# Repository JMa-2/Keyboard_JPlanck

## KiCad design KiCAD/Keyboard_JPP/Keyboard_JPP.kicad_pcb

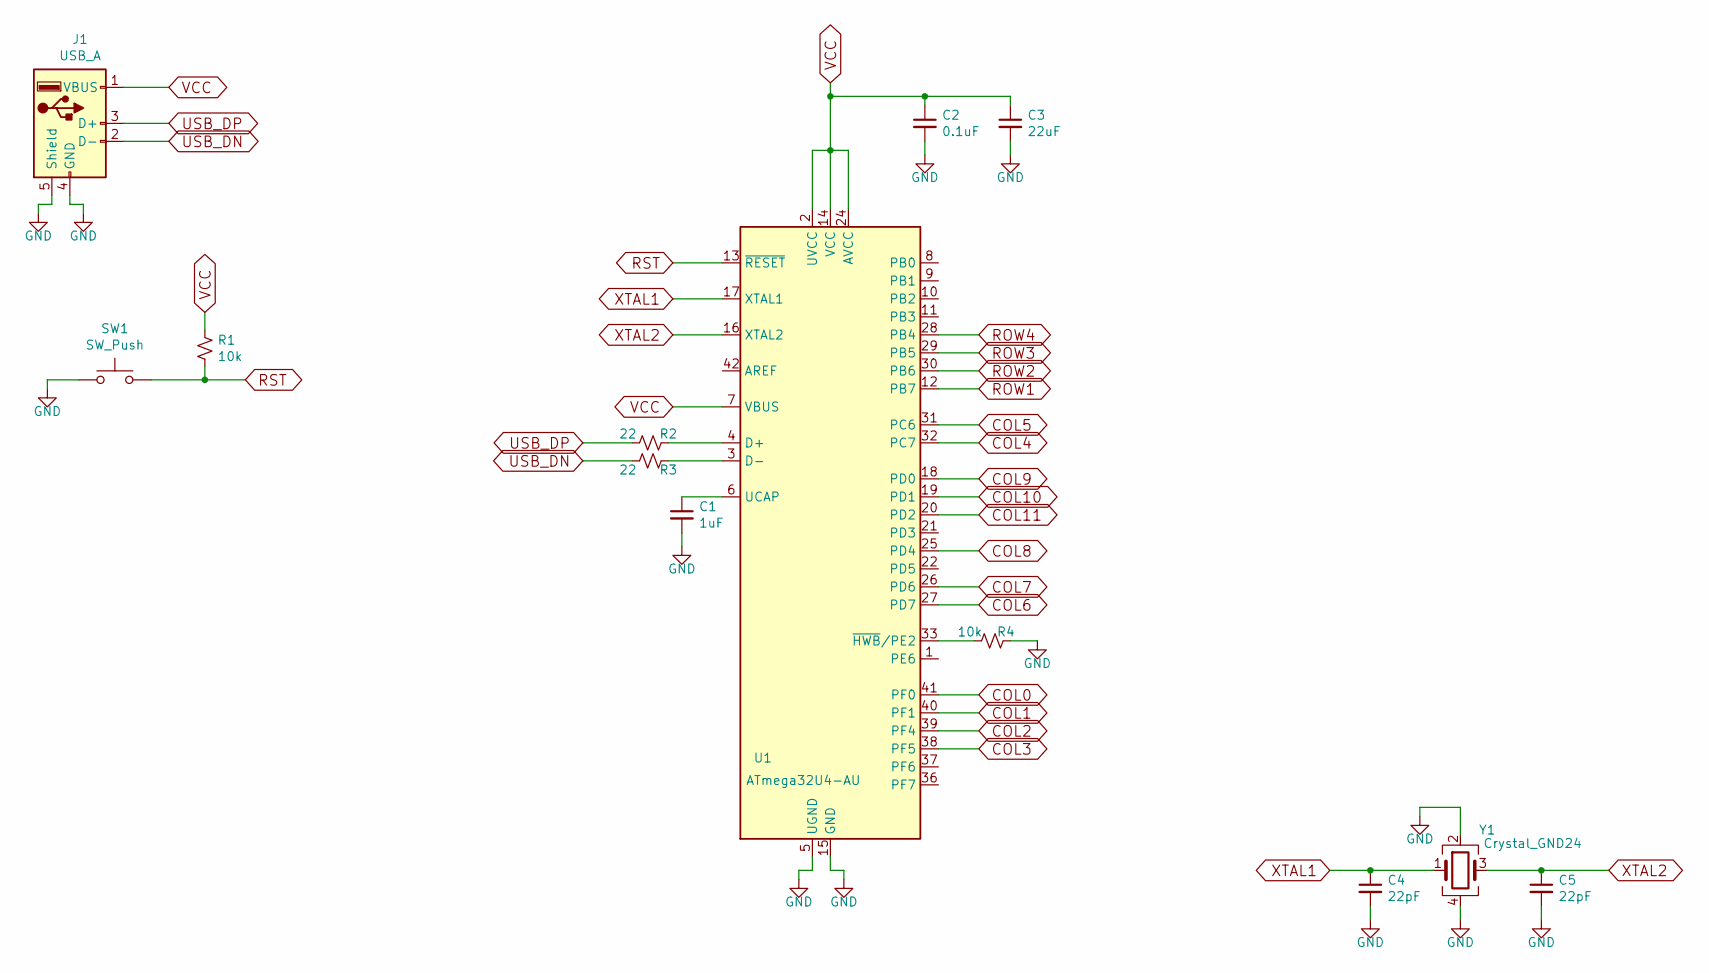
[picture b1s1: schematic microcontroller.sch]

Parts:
C1: 1uF; C_0603_1608Metric
C2: 0.1uF; C_0603_1608Metric
C3: 22uF; C_0603_1608Metric
C4, C5: 22pF; C_0603_1608Metric
J1: USB_A; USB_A_Molex_67643_Horizontal
R1, R4: 10k; R_0805_2012Metric
R2, R3: 22; R_0805_2012Metric
SW1: SW_Push; SW_Push_1P1T_NO_6x6mm_H9.5mm
U1: ATmega32U4-AU; TQFP-44_10x10mm_P0.8mm
Y1: Crystal_GND24; Crystal_SMD_3225-4Pin_3.2x2.5mm_HandSoldering

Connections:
COL0: U1.41 (PF0); also elsewhere on the board
COL1: U1.40 (PF1); also elsewhere on the board
COL2: U1.39 (PF4); also elsewhere on the board
COL3: U1.38 (PF5); also elsewhere on the board
COL4: U1.32 (PC7); also elsewhere on the board
COL5: U1.31 (PC6); also elsewhere on the board
COL6: U1.27 (PD7); also elsewhere on the board
COL7: U1.26 (PD6); also elsewhere on the board
COL8: U1.25 (PD4); also elsewhere on the board
COL9: U1.18 (PD0); also elsewhere on the board
COL10: U1.19 (PD1); also elsewhere on the board
COL11: U1.20 (PD2); also elsewhere on the board
GND: C1.2, C2.2, C3.2, C4.2, C5.2, J1.4 (GND), J1.5 (Shield), R4.1, SW1.1, U1.5 (UGND), U1.15 (GND), U1.23 (GND), U1.35 (GND), U1.43 (GND), Y1.2, Y1.4
unnamed: C1.1, U1.6 (UCAP)
unnamed: R2.1, U1.4 (D+)
unnamed: R3.1, U1.3 (D-)
unnamed: R4.2, U1.33 (~HWB~/PE2)
ROW1: U1.12 (PB7); also elsewhere on the board
ROW2: U1.30 (PB6); also elsewhere on the board
ROW3: U1.29 (PB5); also elsewhere on the board
ROW4: U1.28 (PB4); also elsewhere on the board
RST: R1.2, SW1.2, U1.13 (~RESET)
USB_DN: J1.2 (D-), R3.2
USB_DP: J1.3 (D+), R2.2
VCC: C2.1, C3.1, J1.1 (VBUS), R1.1, U1.2 (UVCC), U1.7 (VBUS), U1.14 (VCC), U1.24 (AVCC), U1.34 (VCC), U1.44 (AVCC)
XTAL1: C4.1, U1.17 (XTAL1), Y1.1
XTAL2: C5.1, U1.16 (XTAL2), Y1.3

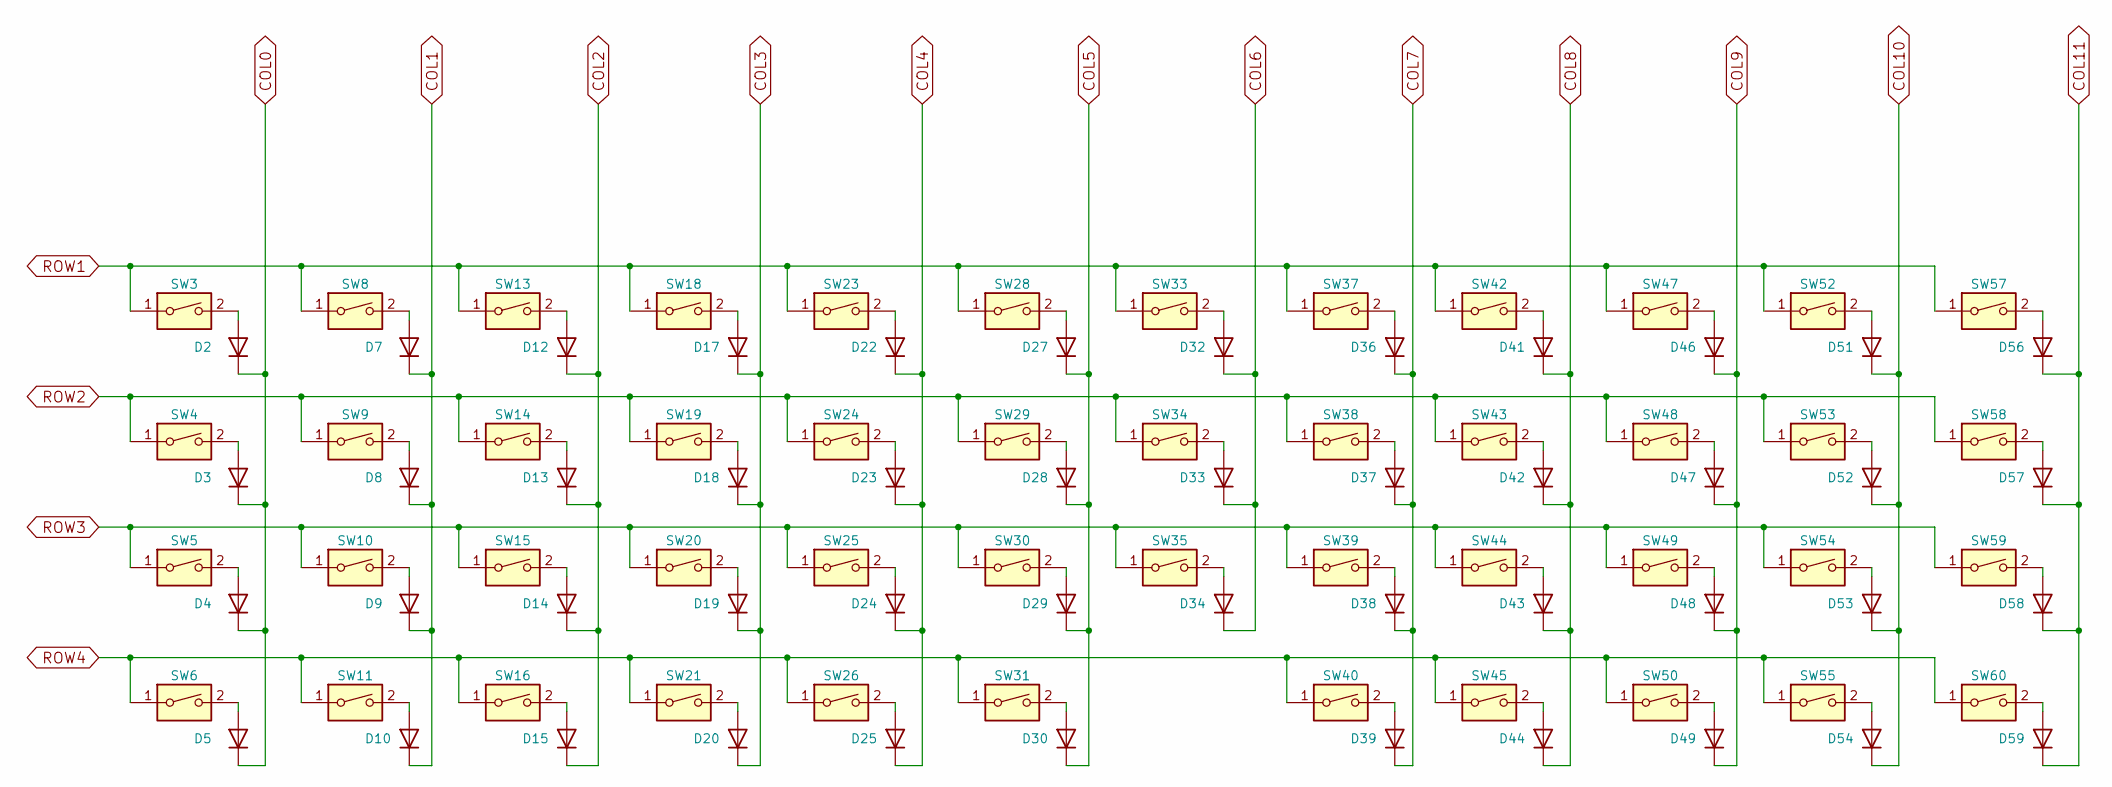
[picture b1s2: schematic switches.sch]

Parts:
D2, D3, D4, D5, D7, D8, D9, D10, D12, D13, D14, D15, D17, D18, D19, D20, D22, D23, D24, D25, D27, D28, D29, D30, D32, D33, D34, D36, D37, D38, D39, D41, D42, D43, D44, D46, D47, D48, D49, D51, D52, D53, D54, D56, D57, D58, D59: 1N4148; D_DO-35_SOD27_P7.62mm_Horizontal
SW3, SW4, SW5, SW6, SW8, SW9, SW10, SW11, SW13, SW14, SW15, SW16, SW18, SW19, SW20, SW21, SW23, SW24, SW25, SW26, SW28, SW29, SW30, SW31, SW33, SW34, SW35, SW37, SW38, SW39, SW40, SW42, SW43, SW44, SW45, SW47, SW48, SW49, SW50, SW52, SW53, SW54, SW55, SW57, SW58, SW59, SW60: SW_DIP_x01; Kailh_socket_MX

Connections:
COL0: D2.1 (K), D3.1 (K), D4.1 (K), D5.1 (K); also elsewhere on the board
COL1: D7.1 (K), D8.1 (K), D9.1 (K), D10.1 (K); also elsewhere on the board
COL2: D12.1 (K), D13.1 (K), D14.1 (K), D15.1 (K); also elsewhere on the board
COL3: D17.1 (K), D18.1 (K), D19.1 (K), D20.1 (K); also elsewhere on the board
COL4: D22.1 (K), D23.1 (K), D24.1 (K), D25.1 (K); also elsewhere on the board
COL5: D27.1 (K), D28.1 (K), D29.1 (K), D30.1 (K); also elsewhere on the board
COL6: D32.1 (K), D33.1 (K), D34.1 (K); also elsewhere on the board
COL7: D36.1 (K), D37.1 (K), D38.1 (K), D39.1 (K); also elsewhere on the board
COL8: D41.1 (K), D42.1 (K), D43.1 (K), D44.1 (K); also elsewhere on the board
COL9: D46.1 (K), D47.1 (K), D48.1 (K), D49.1 (K); also elsewhere on the board
COL10: D51.1 (K), D52.1 (K), D53.1 (K), D54.1 (K); also elsewhere on the board
COL11: D56.1 (K), D57.1 (K), D58.1 (K), D59.1 (K); also elsewhere on the board
unnamed: D2.2 (A), SW3.2
unnamed: D3.2 (A), SW4.2
unnamed: D4.2 (A), SW5.2
unnamed: D5.2 (A), SW6.2
unnamed: D7.2 (A), SW8.2
unnamed: D8.2 (A), SW9.2
unnamed: D9.2 (A), SW10.2
unnamed: D10.2 (A), SW11.2
unnamed: D12.2 (A), SW13.2
unnamed: D13.2 (A), SW14.2
unnamed: D14.2 (A), SW15.2
unnamed: D15.2 (A), SW16.2
unnamed: D17.2 (A), SW18.2
unnamed: D18.2 (A), SW19.2
unnamed: D19.2 (A), SW20.2
unnamed: D20.2 (A), SW21.2
unnamed: D22.2 (A), SW23.2
unnamed: D23.2 (A), SW24.2
unnamed: D24.2 (A), SW25.2
unnamed: D25.2 (A), SW26.2
unnamed: D27.2 (A), SW28.2
unnamed: D28.2 (A), SW29.2
unnamed: D29.2 (A), SW30.2
unnamed: D30.2 (A), SW31.2
unnamed: D32.2 (A), SW33.2
unnamed: D33.2 (A), SW34.2
unnamed: D34.2 (A), SW35.2
unnamed: D36.2 (A), SW37.2
unnamed: D37.2 (A), SW38.2
unnamed: D38.2 (A), SW39.2
unnamed: D39.2 (A), SW40.2
unnamed: D41.2 (A), SW42.2
unnamed: D42.2 (A), SW43.2
unnamed: D43.2 (A), SW44.2
unnamed: D44.2 (A), SW45.2
unnamed: D46.2 (A), SW47.2
unnamed: D47.2 (A), SW48.2
unnamed: D48.2 (A), SW49.2
unnamed: D49.2 (A), SW50.2
unnamed: D51.2 (A), SW52.2
unnamed: D52.2 (A), SW53.2
unnamed: D53.2 (A), SW54.2
unnamed: D54.2 (A), SW55.2
unnamed: D56.2 (A), SW57.2
unnamed: D57.2 (A), SW58.2
unnamed: D58.2 (A), SW59.2
unnamed: D59.2 (A), SW60.2
ROW1: SW3.1, SW8.1, SW13.1, SW18.1, SW23.1, SW28.1, SW33.1, SW37.1, SW42.1, SW47.1, SW52.1, SW57.1; also elsewhere on the board
ROW2: SW4.1, SW9.1, SW14.1, SW19.1, SW24.1, SW29.1, SW34.1, SW38.1, SW43.1, SW48.1, SW53.1, SW58.1; also elsewhere on the board
ROW3: SW5.1, SW10.1, SW15.1, SW20.1, SW25.1, SW30.1, SW35.1, SW39.1, SW44.1, SW49.1, SW54.1, SW59.1; also elsewhere on the board
ROW4: SW6.1, SW11.1, SW16.1, SW21.1, SW26.1, SW31.1, SW40.1, SW45.1, SW50.1, SW55.1, SW60.1; also elsewhere on the board

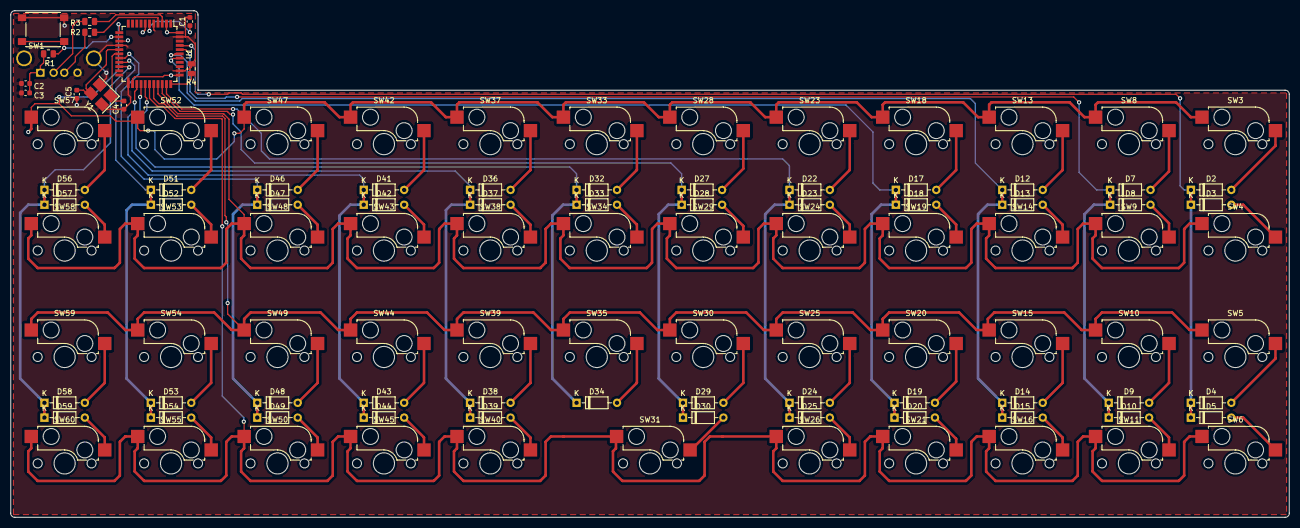
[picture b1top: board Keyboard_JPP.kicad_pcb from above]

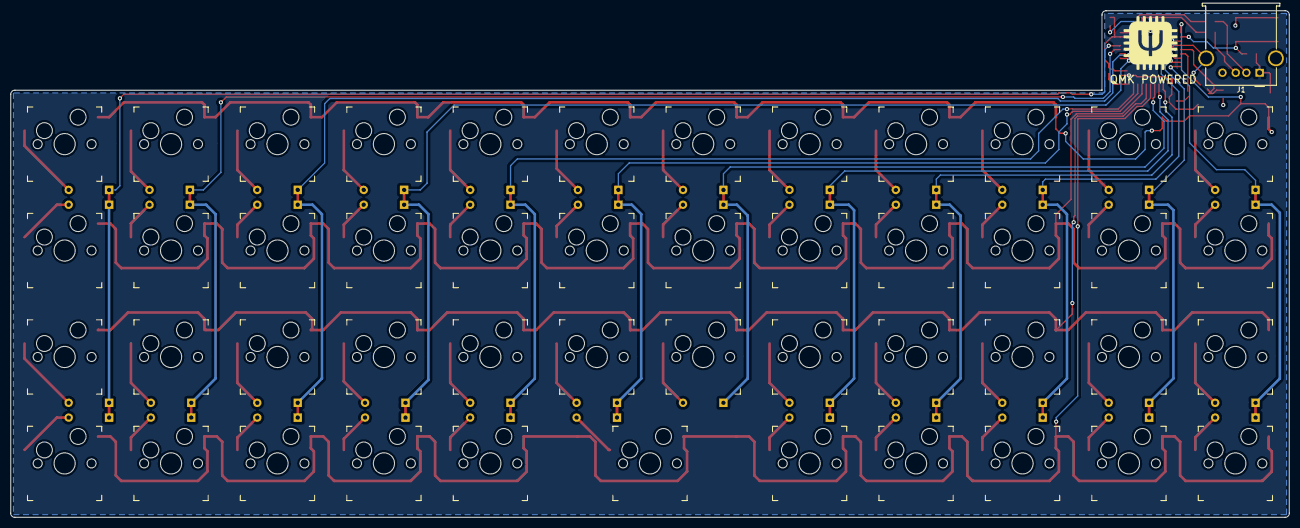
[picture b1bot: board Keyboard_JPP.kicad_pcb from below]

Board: 2 copper layers, 241.0 x 95.5 mm, 107 parts (48 on the bottom side), 74 nets.

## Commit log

2022-06-13 minor key changes
2022-06-13 try 2
